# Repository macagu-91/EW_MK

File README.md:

# EW_MK
*先輩の「電子工作のすすめ」の本をもとにKiCadで回路を作成してみました。

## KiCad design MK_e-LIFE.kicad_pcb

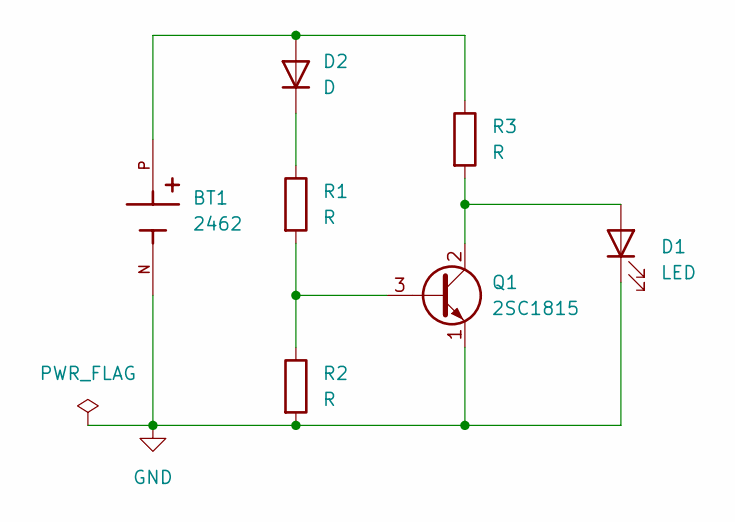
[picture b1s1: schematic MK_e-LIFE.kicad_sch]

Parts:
BT1: 2462; BAT_2462; PARTREV K
D1: LED; LED_D3.0mm
D2: D; CdSセル
Q1: 2SC1815; TO-92_Inline
R1, R2, R3: R; R_Axial_DIN0204_L3.6mm_D1.6mm_P7.62mm_Horizontal

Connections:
GND: BT1.N, D1.1 (K), Q1.1 (E), R2.2
unnamed: D1.2 (A), Q1.2 (C), R3.2
unnamed: BT1.P, D2.2 (A), R3.1
unnamed: D2.1 (K), R1.1
unnamed: Q1.3 (B), R1.2, R2.1

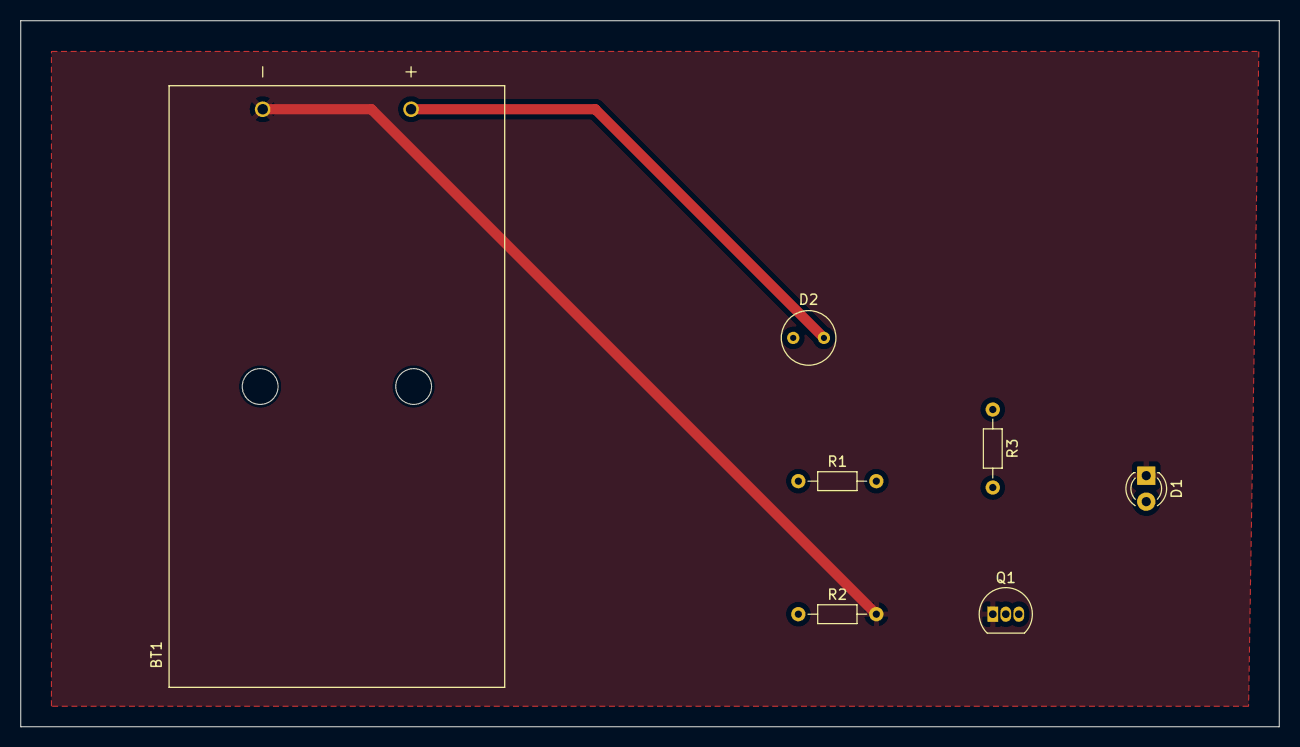
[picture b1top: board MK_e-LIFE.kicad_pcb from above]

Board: 2 copper layers, 123.0 x 69.0 mm, 7 parts (0 on the bottom side), 5 nets.

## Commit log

2025-02-24 READMEの編集
